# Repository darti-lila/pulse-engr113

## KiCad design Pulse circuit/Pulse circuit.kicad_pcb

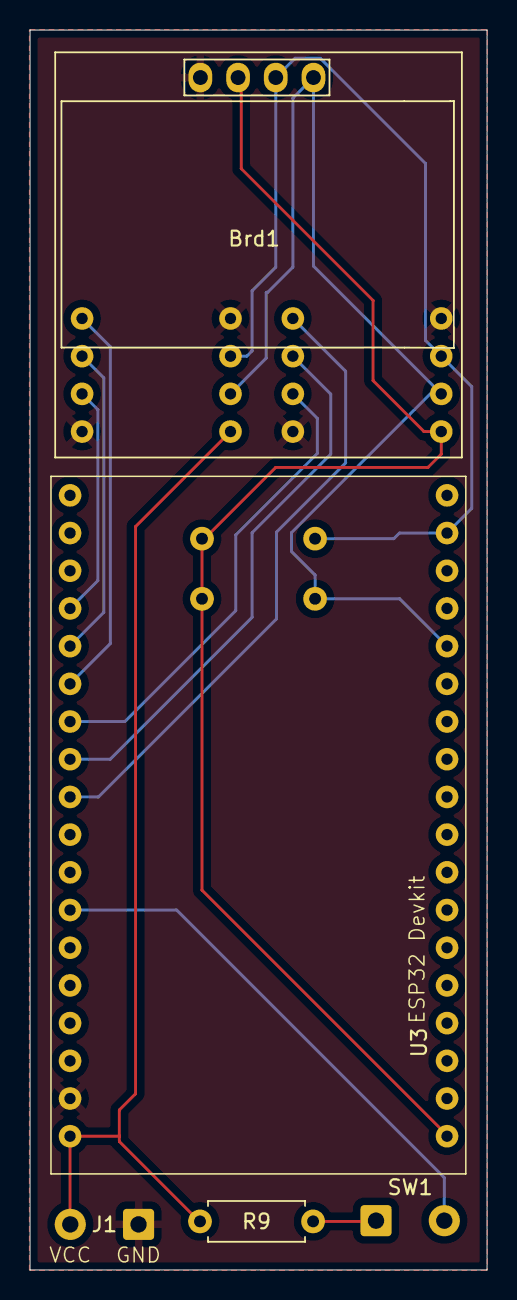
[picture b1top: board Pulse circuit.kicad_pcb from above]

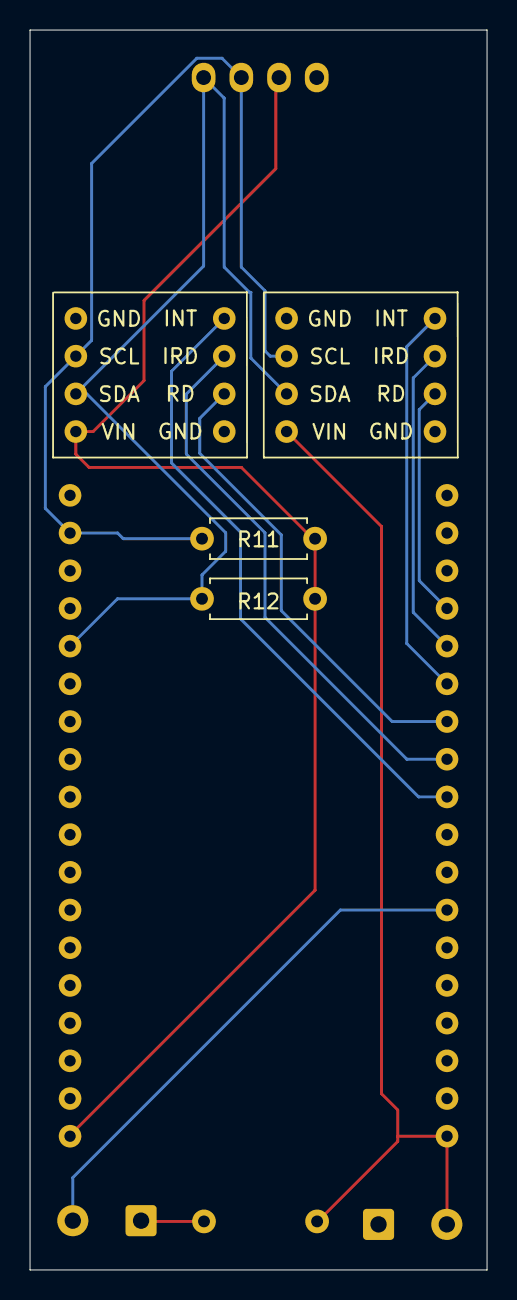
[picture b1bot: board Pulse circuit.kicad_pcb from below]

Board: 2 copper layers, 30.8 x 83.5 mm, 9 parts (4 on the bottom side), 13 nets.

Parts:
Brd1: SSD1306; 128x64OLED
J1: Conn_01x02_Pin; SolderWire-0.5sqmm_1x02_P4.6mm_D0.9mm_OD2.1mm
R9: 1K; R_Axial_DIN0207_L6.3mm_D2.5mm_P7.62mm_Horizontal
R11, R12: 10k; R_Axial_DIN0207_L6.3mm_D2.5mm_P7.62mm_Horizontal
SW1: SW_Push; SolderWire-0.5sqmm_1x02_P4.6mm_D0.9mm_OD2.1mm
U1, U2: module_max30102
U3: DOIT-ESP32-DEVKIT-V1; ESP32-DOIT-DEVKIT

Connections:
3V3: Brd1.2 (VCC), R11.2, R12.2, U1.8, U3.19 (3V3)
5V: J1.2, R9.2, U2.8, U3.18 (VIN)
B: SW1.2, U3.12 (GPIO12_ADC2-CH5_HSPI-MISO_RTC-GPIO15)
GND: Brd1.1 (GND), J1.1, U1.1 (VIN), U1.5 (IRD), U2.1 (VIN), U2.5 (IRD), U3.17 (GND)
INT3v3: U1.4 (INT), U3.9 (GPIO26_ADC2-CH9_DAC2_RTC-GPIO7)
INT5v: U2.4 (INT), U3.6 (GPIO32_ADC1-CH4_RTC-GPIO9)
IRD3v3: U1.3 (SDA), U3.8 (GPIO25_ADC2-CH8_DAC1_RTC-GPIO6)
IRD5v: U2.3 (SDA), U3.5 (GPIO35_ADC1-CH7_RTC-GPIO5)
unnamed: R9.1, SW1.1
RD3v3: U1.2 (SCL), U3.7 (GPIO33_ADC1-CH5_RTC-GPIO8)
RD5v: U2.2 (SCL), U3.4 (GPIO34_ADC1-CH6_RTC-GPIO4)
SCL: Brd1.3 (SCL), R11.1, U1.6 (RD), U2.6 (RD), U3.35 (GPIO22_I2C-SCL)
SDA: Brd1.4 (SDA), R12.1, U1.7 (GND), U2.7 (GND), U3.32 (GPIO21_I2C-SDA)

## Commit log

2025-04-16 Publish circuit begining
2025-04-16 Updated with relative path
    🎯
2025-04-18 uploaded code for the frontend with mock data
2025-04-18 Create frontend
2025-04-18 Organize server folder
2025-04-18 power added
2025-04-18 Power & GND added
2025-04-20 Not finished yet [Will do a revision tomorrow]
2025-04-25 Compacted schematic - No PCB yet
    -Based on Arli's schematic compacted all the wiring. Will attach picture of her wiring to help with the PCB design.
    -Prepared Asila's buck converter schematic, a sheet that can be used to improve the product later with an on board voltage regulator.
2025-05-07 schematic of buck converter
2025-05-07 new buck converter file created
2025-05-08 little changes o the new buck converter
2025-05-14 edited the new buck converter design
2025-05-16 Added 2 pull up resistors
2025-05-16 Changed the R values
2025-05-16 Changed the annotations
2025-05-16 values added to buck converter
2025-05-16 Added footprints for the resistors
2025-05-16 Changed footprint of the resistors
2025-05-18 Heart Rate and Blood Oxygen Code
    Displays heart rate and blood oxygen levels on serial monitor
2025-05-19 Working oxygen and heart rate monitor
    Displays heart rate and blood oxygen levels on oled monitor and serial monitor
2025-05-20 PCB 1/2
2025-05-20 Added a button
2025-05-20 Added the GND plane
2025-05-20 Added the power plane
2025-05-21 new version
2025-05-21 Made some changes
2025-05-23 Rerouted the PCB
2025-05-23 new routes for PCB
2025-05-23 PCB new layer routed
2025-05-23 route changes
2025-05-26 Made some changes to the GND & Power planes
2025-05-27 PCB routes edited
2025-05-28 Final design
    Need to double check size of esp32
